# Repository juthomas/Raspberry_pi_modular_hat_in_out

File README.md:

# Raspberry Pi hat with inputs and outputs for modular synthesizer 

## Schematics

- [Link to pdf](https://github.com/juthomas/Raspberry_pi_modular_hat_in_out/blob/master/Schematics%20PDF/Modular_hat_in_out.pdf)

## Bill Of Materials

- [Link to IBOM](https://juthomas.github.io/Raspberry_pi_modular_hat_in_out/)

## Components

- [MCP3008](https://www.lcsc.com/product-detail/Analog-To-Digital-Converters-ADCs_Microchip-Tech-MCP3008-I-SL_C1520159.html) C1520159

- [LM324](https://www.lcsc.com/product-detail/Operational-Amplifier_STMicroelectronics-LM324DT_C71035.html) C71035

- [MCP4728](https://www.lcsc.com/product-detail/Digital-To-Analog-Converters-DACs_Microchip-Tech-MCP4728-E-UN_C108207.html) C108207

## C code examples (clean naming)

- Input reader: `C_code_example/inputs/src/input_reader.c`
  - binary name: `input_reader`
- Output generator: `C_code_example/outputs/src/output_generator.c`
  - binary name: `output_generator`
- Input/Output loopback tester: `C_code_example/input_outputs/src/input_output_tester.c`
  - binary name: `input_output_tester`

## Install dependencies and configure I2C (recommended)

Use the setup script:

`sudo ./scripts/install_rpi_dependencies.sh --baudrate 1000000`

What it does:

- installs apt dependencies (`build-essential`, `cmake`, `git`, `pkg-config`, `libgpiod-dev`, `i2c-tools`)
- installs [spidev-lib](https://github.com/juthomas/spidev-lib) in `/usr/local`
- sets `dtparam=i2c_arm=on,i2c_arm_baudrate=1000000`
- ensures `dtparam=spi=on`
- keeps a backup of `config.txt` before editing

Reboot is required after running the script.

### Manual install (if needed)

`sudo apt install build-essential cmake git pkg-config libgpiod-dev i2c-tools`

`git clone https://github.com/juthomas/spidev-lib.git`

`cd spidev-lib && mkdir -p build && cd build && cmake .. && make -j$(nproc) && sudo make install`

Do not forget to link with `-lspidev-lib` when compiling C code.

## Shell autocompletion for CLI options

The repository includes completion scripts for:

- `output_generator`
- `input_output_tester`
- `install_rpi_dependencies.sh`

Zsh (current session):

`source scripts/completions/rpi_hat_tools.zsh`

Zsh (persistent):

`echo 'source /absolute/path/to/Raspberry_pi_modular_hat_in_out/scripts/completions/rpi_hat_tools.zsh' >> ~/.zshrc`

Bash (current session):

`source scripts/completions/rpi_hat_tools.bash`

Bash (persistent):

`echo 'source /absolute/path/to/Raspberry_pi_modular_hat_in_out/scripts/completions/rpi_hat_tools.bash' >> ~/.bashrc`

## Build and run

Input side (ADC):

`cd C_code_example/inputs && make && ./input_reader`

With runtime options:

`cd C_code_example/inputs && make && ./input_reader --delay-us=100000`

Dashboard cadence is controlled in source with `EQUALIZER_EVERY` and `HISTORY_EVERY` in `C_code_example/inputs/src/input_reader.c`.

Output side (MCP4728):

`cd C_code_example/outputs && make && ./output_generator`

With runtime options:

`cd C_code_example/outputs && make && ./output_generator --resolution=1000 --delay-us=1`

Dashboard cadence is controlled in source with `EQUALIZER_EVERY` and `HISTORY_EVERY` in `C_code_example/outputs/src/output_generator.c`.

Input/Output combined test (MCP4728 sine with per-channel phase + ADS monitoring):

`cd C_code_example/input_outputs && make && ./input_output_tester --resolution=1000 --delay-us=1`

Dashboard cadence is controlled in source with `EQUALIZER_EVERY` and `HISTORY_EVERY` in `C_code_example/input_outputs/src/input_output_tester.c`.

## Electrical Voltage dividers & multiplier

### Divider
https://tinyurl.com/24boqd2k

### Multiplier
<!-- https://tinyurl.com/27d8ra9q -->
https://tinyurl.com/2aczbd22

https://github.com/WiringPi/WiringPi

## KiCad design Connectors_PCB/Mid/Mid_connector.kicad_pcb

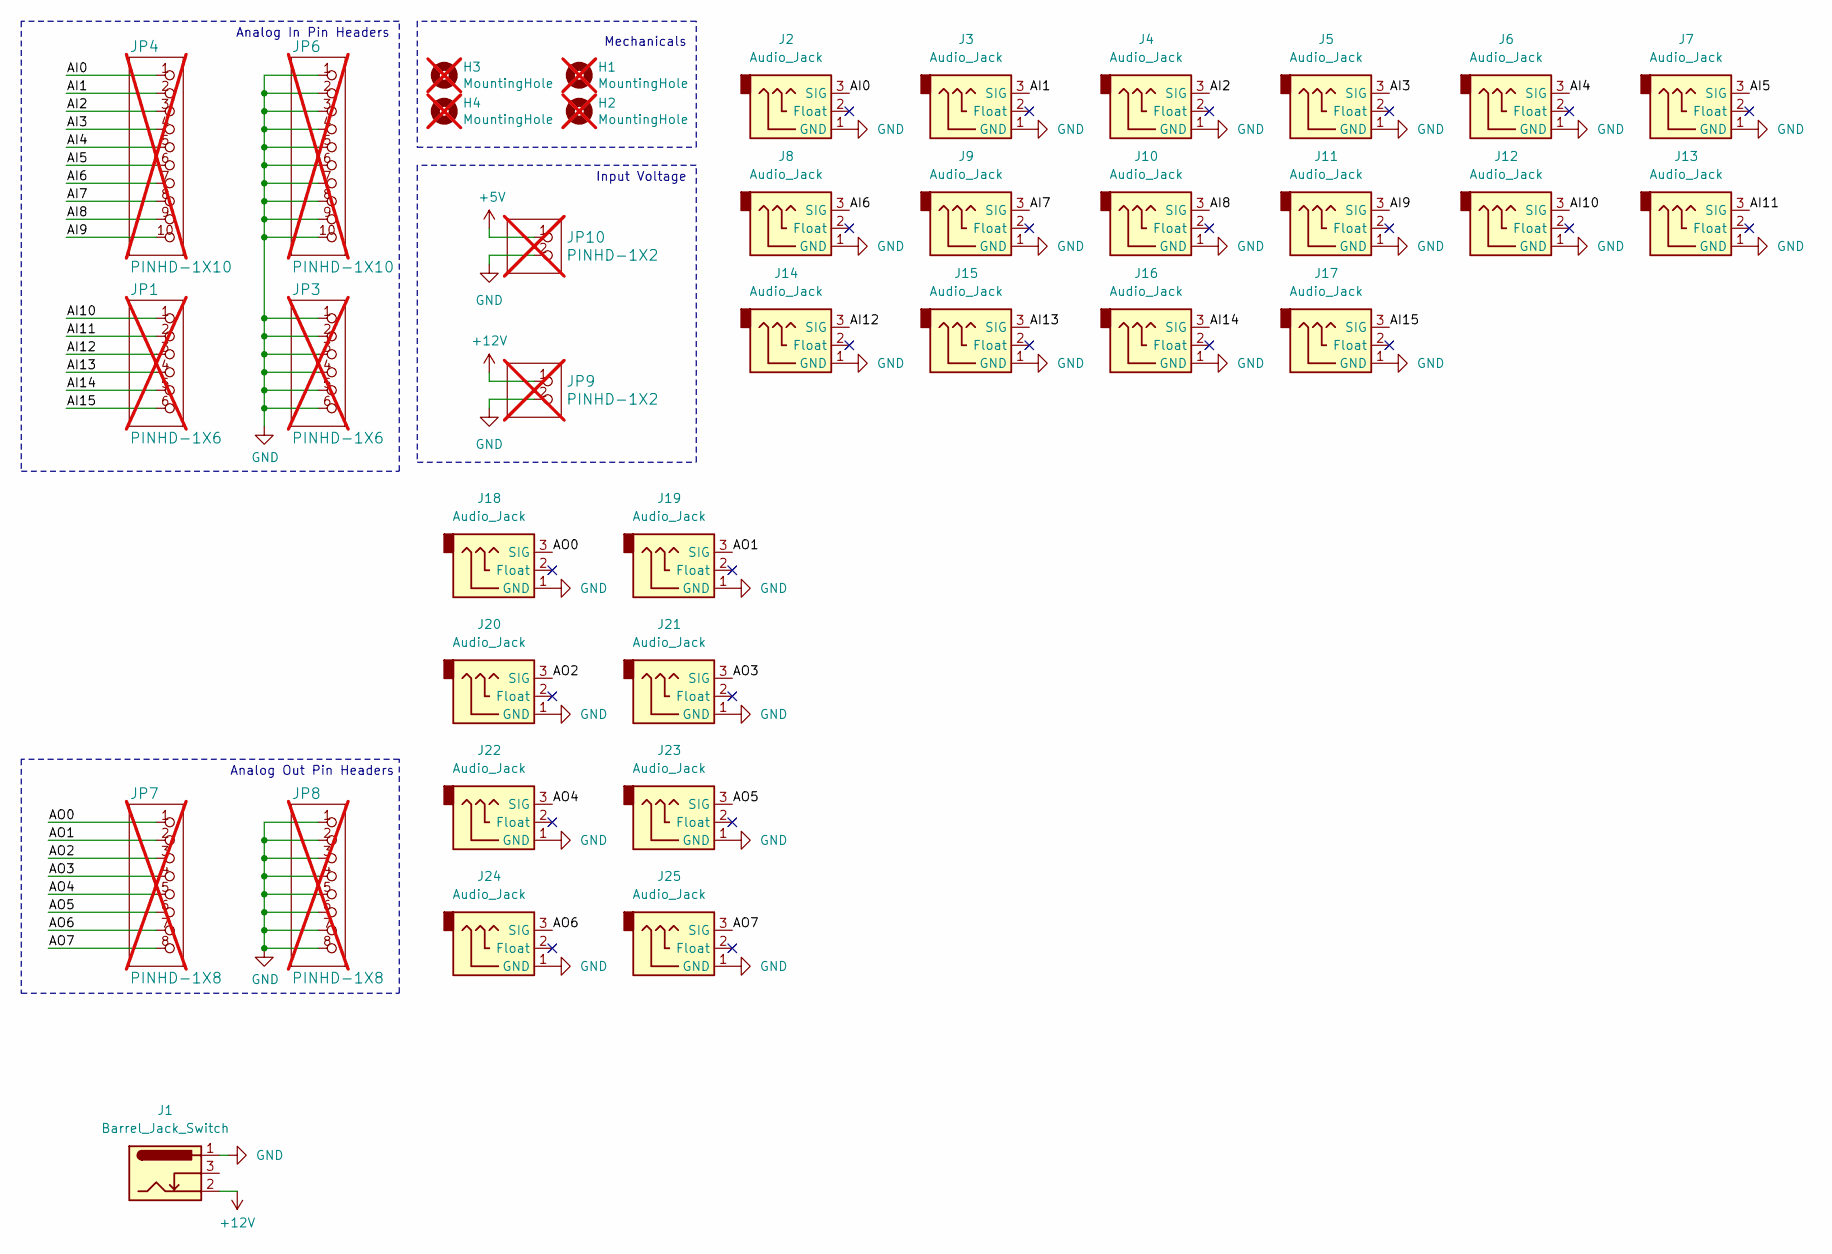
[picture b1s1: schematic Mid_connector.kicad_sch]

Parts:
H1, H2, H3, H4: MountingHole; MountingHole_2.7mm_M2.5; not fitted
J1: Barrel_Jack_Switch; DC_Jack_2.1
J2, J3, J4, J5, J6, J7, J8, J9, J10, J11, J12, J13, J14, J15, J16, J17, J18, J19, J20, J21, J22, J23, J24, J25: Audio_Jack; Mini_Jack
JP1, JP3: PINHD-1X6; 1X06-BIG; not fitted
JP4, JP6: PINHD-1X10; 1X10-BIG; not fitted
JP7, JP8: PINHD-1X8; 1X08-BIG; not fitted
JP9, JP10: PINHD-1X2; 1X02-BIG; not fitted

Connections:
+5V: JP10.1
+12V: J1.2, JP9.1
/AI0: J2.3 (SIG), JP4.1
/AI1: J3.3 (SIG), JP4.2
/AI2: J4.3 (SIG), JP4.3
/AI3: J5.3 (SIG), JP4.4
/AI4: J6.3 (SIG), JP4.5
/AI5: J7.3 (SIG), JP4.6
/AI6: J8.3 (SIG), JP4.7
/AI7: J9.3 (SIG), JP4.8
/AI8: J10.3 (SIG), JP4.9
/AI9: J11.3 (SIG), JP4.10
/AI10: J12.3 (SIG), JP1.1
/AI11: J13.3 (SIG), JP1.2
/AI12: J14.3 (SIG), JP1.3
/AI13: J15.3 (SIG), JP1.4
/AI14: J16.3 (SIG), JP1.5
/AI15: J17.3 (SIG), JP1.6
/AO0: J18.3 (SIG), JP7.1
/AO1: J19.3 (SIG), JP7.2
/AO2: J20.3 (SIG), JP7.3
/AO3: J21.3 (SIG), JP7.4
/AO4: J22.3 (SIG), JP7.5
/AO5: J23.3 (SIG), JP7.6
/AO6: J24.3 (SIG), JP7.7
/AO7: J25.3 (SIG), JP7.8
GND: J1.1, J2.1 (GND), J3.1 (GND), J4.1 (GND), J5.1 (GND), J6.1 (GND), J7.1 (GND), J8.1 (GND), J9.1 (GND), J10.1 (GND), J11.1 (GND), J12.1 (GND), J13.1 (GND), J14.1 (GND), J15.1 (GND), J16.1 (GND), J17.1 (GND), J18.1 (GND), J19.1 (GND), J20.1 (GND), J21.1 (GND), J22.1 (GND), J23.1 (GND), J24.1 (GND), J25.1 (GND), JP3.1, JP3.2, JP3.3, JP3.4, JP3.5, JP3.6, JP6.1, JP6.2, JP6.3, JP6.4, JP6.5, JP6.6, JP6.7, JP6.8, JP6.9, JP6.10, JP8.1, JP8.2, JP8.3, JP8.4, JP8.5, JP8.6, JP8.7, JP8.8, JP9.2, JP10.2

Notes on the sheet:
Analog Out Pin Headers
Mechanicals
Input Voltage
Analog In Pin Headers

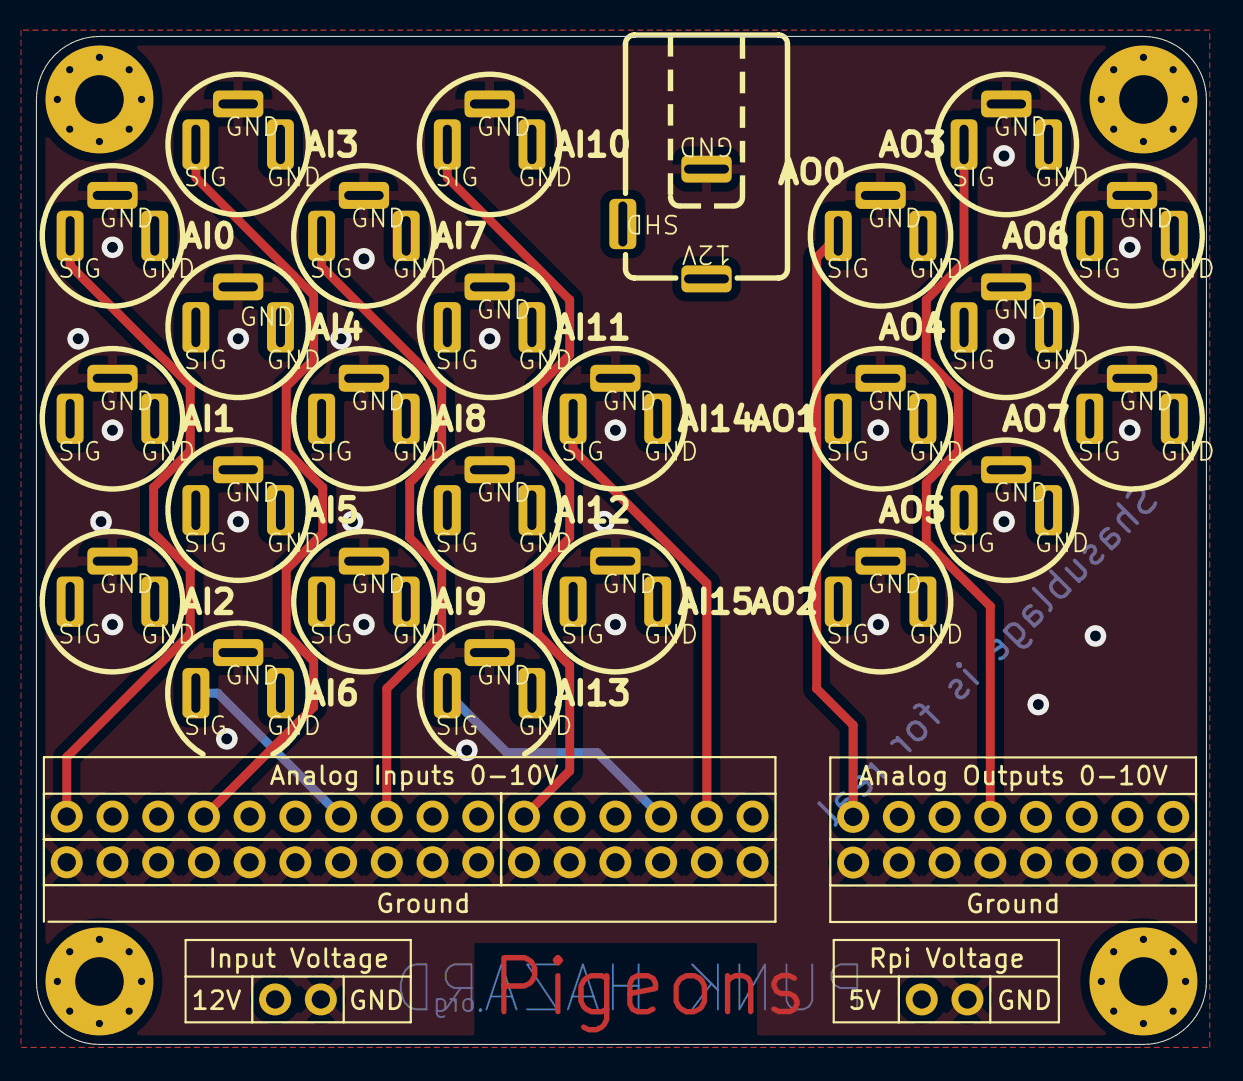
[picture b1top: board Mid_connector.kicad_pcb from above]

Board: 4 copper layers, 65.0 x 56.0 mm, 37 parts (0 on the bottom side), 26 nets.

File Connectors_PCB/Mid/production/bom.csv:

Designator,Footprint,Quantity,Value,LCSC Part #
J1,DC_Jack_2.1,1,Barrel_Jack_Switch,
"J10, J11, J12, J13, J14, J15, J16, J17, J18, J19, J2, J20, J21, J22, J23, J24, J25, J3, J4, J5, J6, J7, J8, J9",Mini_Jack,24,Audio_Jack,
"JP10, JP9",1X02-BIG,2,PINHD-1X2,

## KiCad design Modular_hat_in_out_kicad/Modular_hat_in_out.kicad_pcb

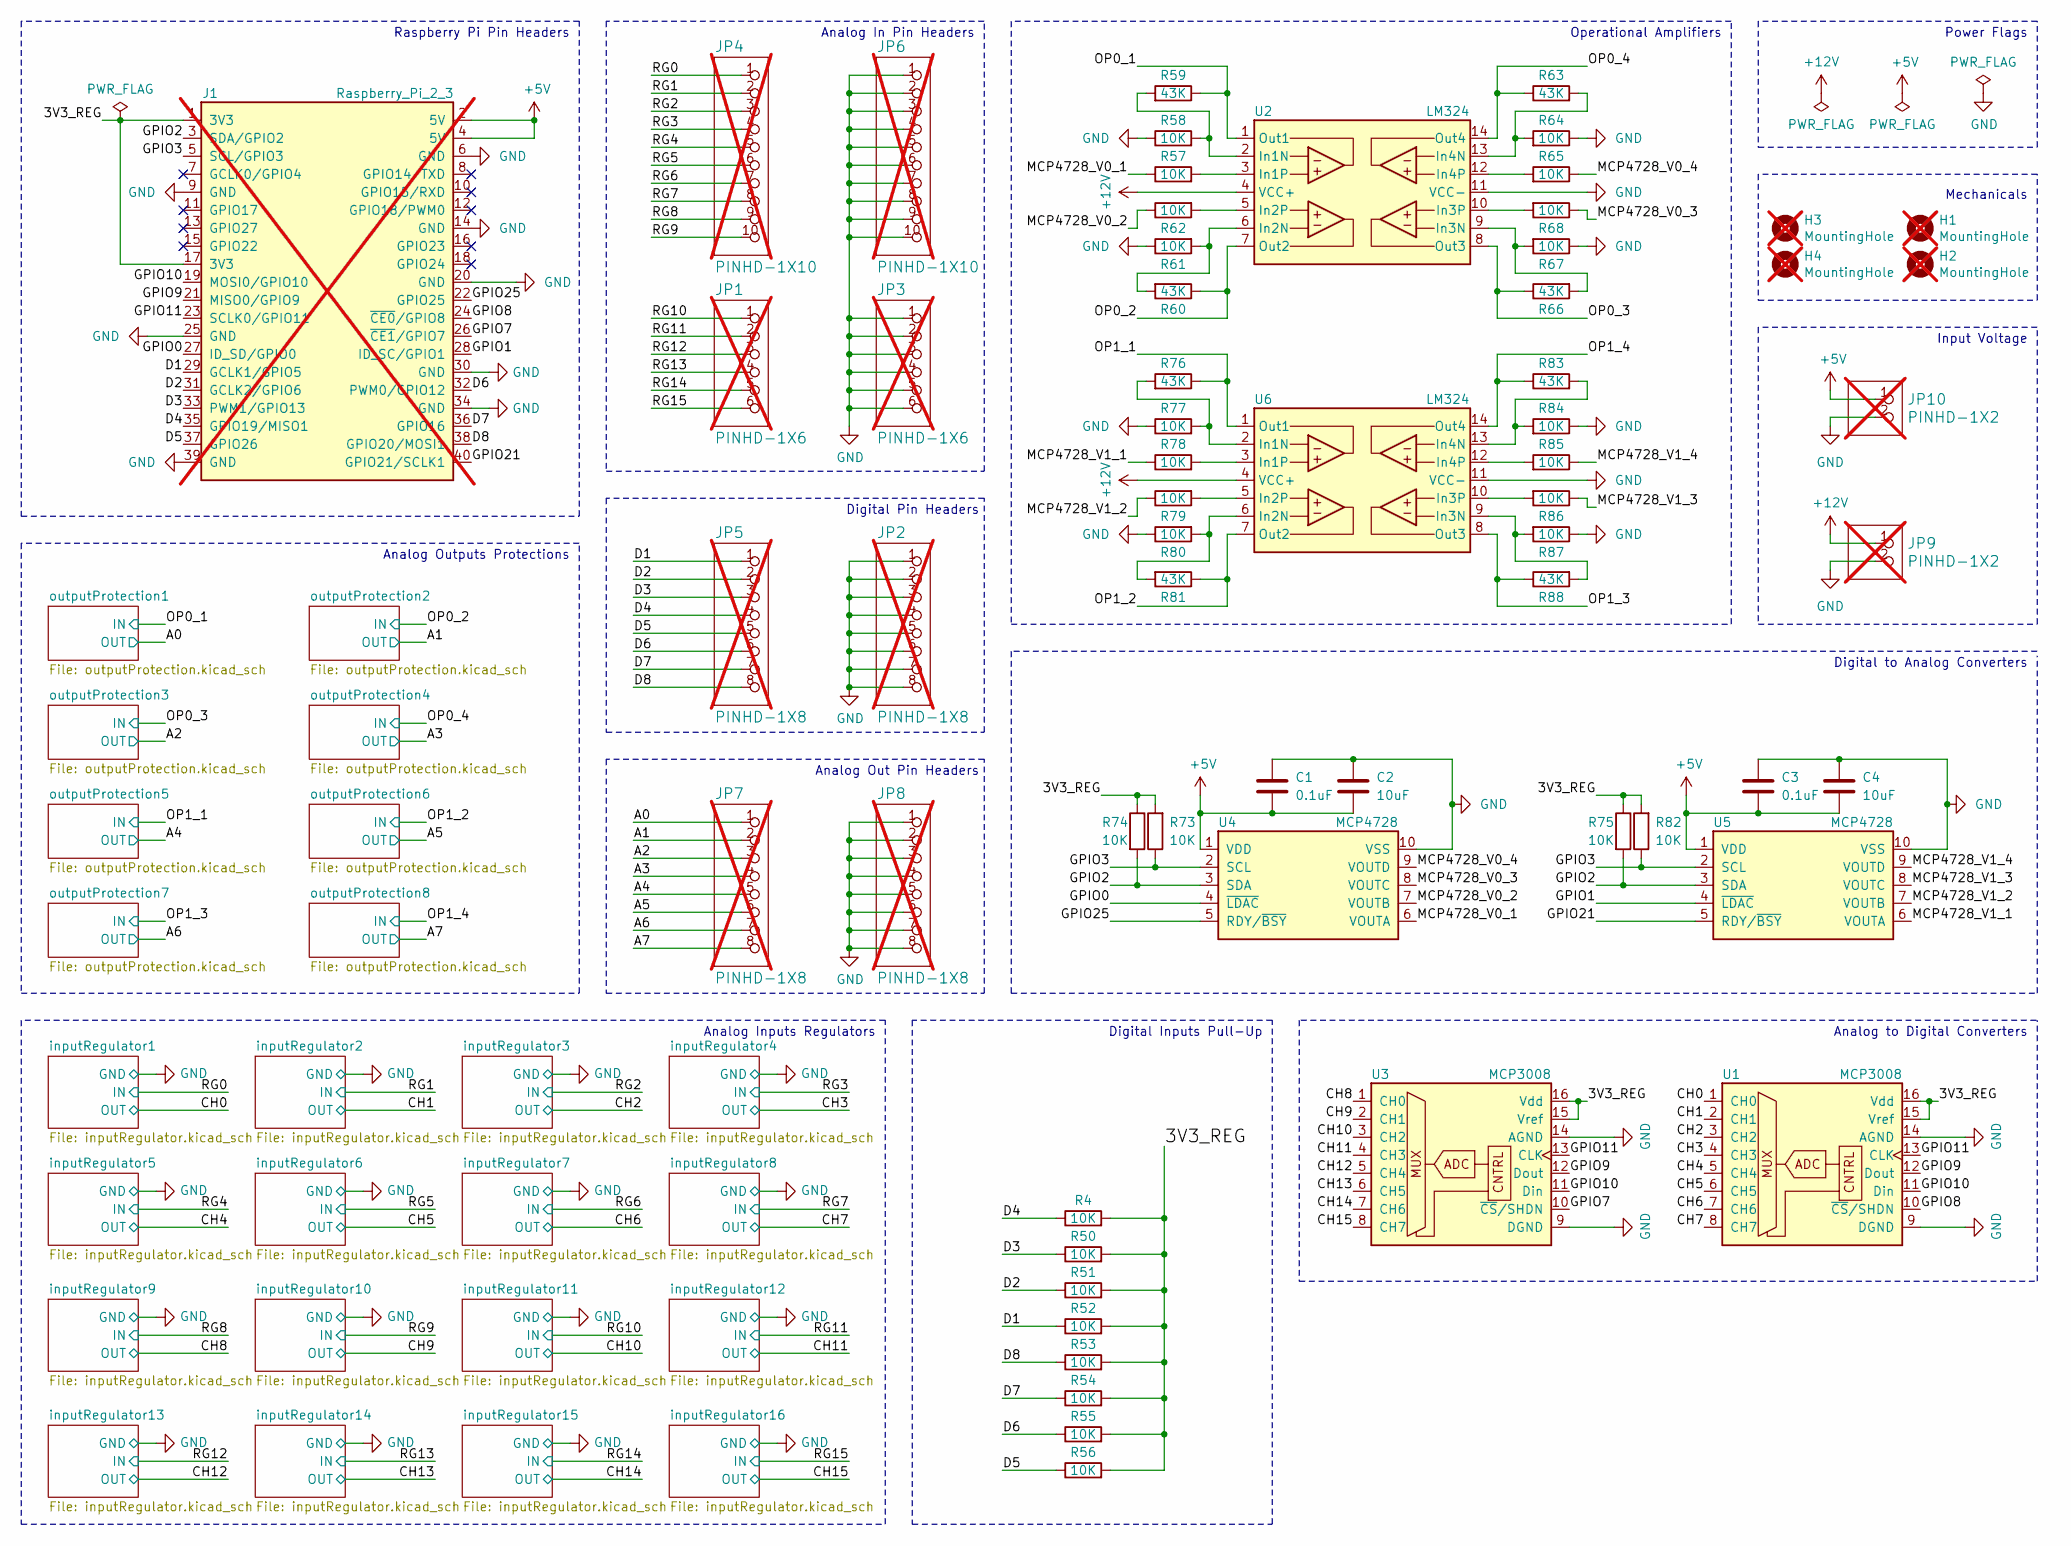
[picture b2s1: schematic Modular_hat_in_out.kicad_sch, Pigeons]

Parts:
C1, C3: 0.1uF; C_0603_1608Metric; LCSC C14663
C2, C4: 10uF; C_0603_1608Metric; LCSC C1691
H1, H2, H3, H4: MountingHole; MountingHole_2.7mm_M2.5; not fitted
J1: Raspberry_Pi_2_3; PIN_20X2; not fitted
JP1, JP3: PINHD-1X6; 1X06-BIG; not fitted
JP2, JP5, JP7, JP8: PINHD-1X8; 1X08-BIG; not fitted
JP4, JP6: PINHD-1X10; 1X10-BIG; not fitted
JP9, JP10: PINHD-1X2; 1X02-BIG; not fitted
R4, R50, R51, R52, R53, R54, R55, R56, R57, R58, R61, R62, R64, R65, R67, R68, R73, R74, R75, R77, R78, R79, R80, R82, R84, R85, R86, R87: 10K; R_0603_1608Metric; LCSC C25804
R59, R60, R63, R66, R76, R81, R83, R88: 43K; R_0603_1608Metric; LCSC C23172
U1, U3: MCP3008; MCP3008 SOIC16; LCSC C1520159
U2, U6: LM324; LM324 SOIC14; LCSC C71035
U4, U5: MCP4728; MCP4728 MSOP10; LCSC C108207

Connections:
+5V: C1.1, C2.1, C3.1, C4.1, J1.2 (5V), J1.4 (5V), JP10.1, U4.1 (VDD), U5.1 (VDD)
+12V: JP9.1, U2.4 (VCC+), U6.4 (VCC+)
/3V3_REG: J1.1 (3V3), J1.17 (3V3), R4.2, R50.2, R51.2, R52.2, R53.2, R54.2, R55.2, R56.2, R73.2, R74.1, R75.1, R82.2, U1.15 (Vref), U1.16 (Vdd), U3.15 (Vref), U3.16 (Vdd)
/A0: JP7.1; also elsewhere on the board
/A1: JP7.2; also elsewhere on the board
/A2: JP7.3; also elsewhere on the board
/A3: JP7.4; also elsewhere on the board
/A4: JP7.5; also elsewhere on the board
/A5: JP7.6; also elsewhere on the board
/A6: JP7.7; also elsewhere on the board
/A7: JP7.8; also elsewhere on the board
/CH0: U1.1 (CH0); also elsewhere on the board
/CH1: U1.2 (CH1); also elsewhere on the board
/CH2: U1.3 (CH2); also elsewhere on the board
/CH3: U1.4 (CH3); also elsewhere on the board
/CH4: U1.5 (CH4); also elsewhere on the board
/CH5: U1.6 (CH5); also elsewhere on the board
/CH6: U1.7 (CH6); also elsewhere on the board
/CH7: U1.8 (CH7); also elsewhere on the board
/CH8: U3.1 (CH0); also elsewhere on the board
/CH9: U3.2 (CH1); also elsewhere on the board
/CH10: U3.3 (CH2); also elsewhere on the board
/CH11: U3.4 (CH3); also elsewhere on the board
/CH12: U3.5 (CH4); also elsewhere on the board
/CH13: U3.6 (CH5); also elsewhere on the board
/CH14: U3.7 (CH6); also elsewhere on the board
/CH15: U3.8 (CH7); also elsewhere on the board
/D1: J1.29 (GCLK1/GPIO5), JP5.1, R52.1
/D2: J1.31 (GCLK2/GPIO6), JP5.2, R51.1
/D3: J1.33 (PWM1/GPIO13), JP5.3, R50.1
/D4: J1.35 (GPIO19/MISO1), JP5.4, R4.1
/D5: J1.37 (GPIO26), JP5.5, R56.1
/D6: J1.32 (PWM0/GPIO12), JP5.6, R55.1
/D7: J1.36 (GPIO16), JP5.7, R54.1
/D8: J1.38 (GPIO20/MOSI1), JP5.8, R53.1
/GPIO0: J1.27 (ID_SD/GPIO0), U4.4 (~LDAC)
/GPIO1: J1.28 (ID_SC/GPIO1), U5.4 (~LDAC)
/GPIO2: J1.3 (SDA/GPIO2), R74.2, R75.2, U4.3 (SDA), U5.3 (SDA)
/GPIO3: J1.5 (SCL/GPIO3), R73.1, R82.1, U4.2 (SCL), U5.2 (SCL)
/GPIO7: J1.26 (~CE1/GPIO7), U3.10 (~CS/SHDN)
/GPIO8: J1.24 (~CE0/GPIO8), U1.10 (~CS/SHDN)
/GPIO9: J1.21 (MISO0/GPIO9), U1.12 (Dout), U3.12 (Dout)
/GPIO10: J1.19 (MOSI0/GPIO10), U1.11 (Din), U3.11 (Din)
/GPIO11: J1.23 (SCLK0/GPIO11), U1.13 (CLK), U3.13 (CLK)
/GPIO21: J1.40 (GPIO21/SCLK1), U5.5 (RDY/~BSY)
/GPIO25: J1.22 (GPIO25), U4.5 (RDY/~BSY)
/MCP4728_V0_1: R57.1, U4.6 (VOUTA)
/MCP4728_V0_2: R62.1, U4.7 (VOUTB)
/MCP4728_V0_3: R68.1, U4.8 (VOUTC)
/MCP4728_V0_4: R65.1, U4.9 (VOUTD)
/MCP4728_V1_1: R78.1, U5.6 (VOUTA)
/MCP4728_V1_2: R79.1, U5.7 (VOUTB)
/MCP4728_V1_3: R86.1, U5.8 (VOUTC)
/MCP4728_V1_4: R85.1, U5.9 (VOUTD)
/OP0_1: R59.2, U2.1 (Out1); also elsewhere on the board
/OP0_2: R60.2, U2.7 (Out2); also elsewhere on the board
/OP0_3: R66.2, U2.8 (Out3); also elsewhere on the board
/OP0_4: R63.2, U2.14 (Out4); also elsewhere on the board
/OP1_1: R76.2, U6.1 (Out1); also elsewhere on the board
/OP1_2: R81.2, U6.7 (Out2); also elsewhere on the board
/OP1_3: R88.2, U6.8 (Out3); also elsewhere on the board
/OP1_4: R83.2, U6.14 (Out4); also elsewhere on the board
/RG0: JP4.1; also elsewhere on the board
/RG1: JP4.2; also elsewhere on the board
/RG2: JP4.3; also elsewhere on the board
/RG3: JP4.4; also elsewhere on the board
/RG4: JP4.5; also elsewhere on the board
/RG5: JP4.6; also elsewhere on the board
/RG6: JP4.7; also elsewhere on the board
/RG7: JP4.8; also elsewhere on the board
/RG8: JP4.9; also elsewhere on the board
/RG9: JP4.10; also elsewhere on the board
/RG10: JP1.1; also elsewhere on the board
/RG11: JP1.2; also elsewhere on the board
/RG12: JP1.3; also elsewhere on the board
/RG13: JP1.4; also elsewhere on the board
/RG14: JP1.5; also elsewhere on the board
/RG15: JP1.6; also elsewhere on the board
GND: C1.2, C2.2, C3.2, C4.2, J1.6 (GND), J1.9 (GND), J1.14 (GND), J1.20 (GND), J1.25 (GND), J1.30 (GND), J1.34 (GND), J1.39 (GND), JP2.1, JP2.2, JP2.3, JP2.4, JP2.5, JP2.6, JP2.7, JP2.8, JP3.1, JP3.2, JP3.3, JP3.4, JP3.5, JP3.6, JP6.1, JP6.2, JP6.3, JP6.4, JP6.5, JP6.6, JP6.7, JP6.8, JP6.9, JP6.10, JP8.1, JP8.2, JP8.3, JP8.4, JP8.5, JP8.6, JP8.7, JP8.8, JP9.2, JP10.2, R58.1, R61.1, R64.1, R67.1, R77.1, R80.1, R84.1, R87.1, U1.9 (DGND), U1.14 (AGND), U2.11 (VCC-), U3.9 (DGND), U3.14 (AGND), U4.10 (VSS), U5.10 (VSS), U6.11 (VCC-); also elsewhere on the board
unnamed: R58.2, R59.1, U2.2 (In1N)
unnamed: R57.2, U2.3 (In1P)
unnamed: R60.1, R61.2, U2.6 (In2N)
unnamed: R62.2, U2.5 (In2P)
unnamed: R66.1, R67.2, U2.9 (In3N)
unnamed: R68.2, U2.10 (In3P)
unnamed: R63.1, R64.2, U2.13 (In4N)
unnamed: R65.2, U2.12 (In4P)
unnamed: R76.1, R77.2, U6.2 (In1N)
unnamed: R78.2, U6.3 (In1P)
unnamed: R80.2, R81.1, U6.6 (In2N)
unnamed: R79.2, U6.5 (In2P)
unnamed: R87.2, R88.1, U6.9 (In3N)
unnamed: R86.2, U6.10 (In3P)
unnamed: R83.1, R84.2, U6.13 (In4N)
unnamed: R85.2, U6.12 (In4P)

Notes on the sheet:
Analog Outputs Protections
Digital Inputs Pull-Up
Analog Out Pin Headers
Raspberry Pi Pin Headers
Operational Amplifiers
Input Voltage
Mechanicals
Analog Inputs Regulators
Digital Pin Headers
Digital to Analog Converters
Analog In Pin Headers
Analog to Digital Converters
Power Flags

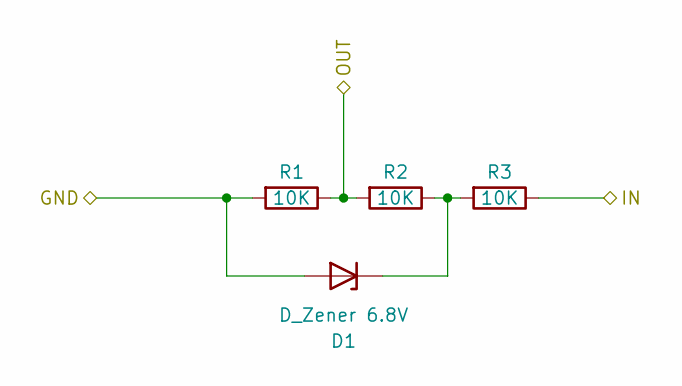
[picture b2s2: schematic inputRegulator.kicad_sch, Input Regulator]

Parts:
D1: D_Zener 6.8V; D_Z_0603_1608Metric; LCSC C2832575
R1, R2, R3: 10K; R_0603_1608Metric; LCSC C25804

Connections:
/CH0: R1.1, R2.2; also elsewhere on the board
/RG0: R3.1; also elsewhere on the board
GND: D1.2 (A), R1.2; also elsewhere on the board
unnamed: D1.1 (K), R2.1, R3.2

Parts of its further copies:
D2, D3, D4, D5, D6, D7, D8, D9, D10, D11, D12, D13, D14, D15, D16: D_Zener 6.8V; D_Z_0603_1608Metric; LCSC C2832575
R5, R6, R7, R8, R9, R10, R11, R12, R13, R14, R15, R16, R17, R18, R19, R20, R21, R22, R23, R24, R25, R26, R27, R28, R29, R30, R31, R32, R33, R34, R35, R36, R37, R38, R39, R40, R41, R42, R43, R44, R45, R46, R47, R48, R49: 10K; R_0603_1608Metric; LCSC C25804

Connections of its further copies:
/CH1: R5.1, R6.2; also elsewhere on the board
/CH2: R8.1, R9.2; also elsewhere on the board
/CH3: R11.1, R12.2; also elsewhere on the board
/CH4: R14.1, R15.2; also elsewhere on the board
/CH5: R17.1, R18.2; also elsewhere on the board
/CH6: R20.1, R21.2; also elsewhere on the board
/CH7: R23.1, R24.2; also elsewhere on the board
/CH8: R26.1, R27.2; also elsewhere on the board
/CH9: R29.1, R30.2; also elsewhere on the board
/CH10: R32.1, R33.2; also elsewhere on the board
/CH11: R35.1, R36.2; also elsewhere on the board
/CH12: R38.1, R39.2; also elsewhere on the board
/CH13: R41.1, R42.2; also elsewhere on the board
/CH14: R44.1, R45.2; also elsewhere on the board
/CH15: R47.1, R48.2; also elsewhere on the board
/RG1: R7.1; also elsewhere on the board
/RG2: R10.1; also elsewhere on the board
/RG3: R13.1; also elsewhere on the board
/RG4: R16.1; also elsewhere on the board
/RG5: R19.1; also elsewhere on the board
/RG6: R22.1; also elsewhere on the board
/RG7: R25.1; also elsewhere on the board
/RG8: R28.1; also elsewhere on the board
/RG9: R31.1; also elsewhere on the board
/RG10: R34.1; also elsewhere on the board
/RG11: R37.1; also elsewhere on the board
/RG12: R40.1; also elsewhere on the board
/RG13: R43.1; also elsewhere on the board
/RG14: R46.1; also elsewhere on the board
/RG15: R49.1; also elsewhere on the board
GND: D2.2 (A), D3.2 (A), D4.2 (A), D5.2 (A), D6.2 (A), D7.2 (A), D8.2 (A), D9.2 (A), D10.2 (A), D11.2 (A), D12.2 (A), D13.2 (A), D14.2 (A), D15.2 (A), D16.2 (A), R5.2, R8.2, R11.2, R14.2, R17.2, R20.2, R23.2, R26.2, R29.2, R32.2, R35.2, R38.2, R41.2, R44.2, R47.2; also elsewhere on the board
unnamed: D2.1 (K), R6.1, R7.2
unnamed: D3.1 (K), R9.1, R10.2
unnamed: D4.1 (K), R12.1, R13.2
unnamed: D5.1 (K), R15.1, R16.2
unnamed: D6.1 (K), R18.1, R19.2
unnamed: D7.1 (K), R21.1, R22.2
unnamed: D8.1 (K), R24.1, R25.2
unnamed: D9.1 (K), R27.1, R28.2
unnamed: D10.1 (K), R30.1, R31.2
unnamed: D11.1 (K), R33.1, R34.2
unnamed: D12.1 (K), R36.1, R37.2
unnamed: D13.1 (K), R39.1, R40.2
unnamed: D14.1 (K), R42.1, R43.2
unnamed: D15.1 (K), R45.1, R46.2
unnamed: D16.1 (K), R48.1, R49.2

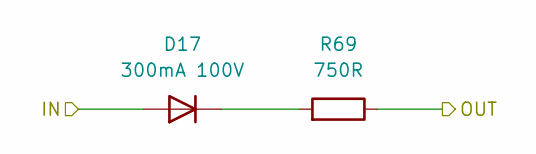
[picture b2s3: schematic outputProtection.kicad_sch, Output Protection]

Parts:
D17: 300mA 100V; D_0603_1608Metric; LCSC C727112
R69: 750R; R_0603_1608Metric; LCSC C23241

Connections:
/A0: R69.2; also elsewhere on the board
/OP0_1: D17.2 (A); also elsewhere on the board
unnamed: D17.1 (K), R69.1

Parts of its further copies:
D18, D19, D20, D21, D22, D23, D24: 300mA 100V; D_0603_1608Metric; LCSC C727112
R70, R71, R72, R89, R90, R91, R92: 750R; R_0603_1608Metric; LCSC C23241

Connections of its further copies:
/A1: R70.2; also elsewhere on the board
/A2: R71.2; also elsewhere on the board
/A3: R72.2; also elsewhere on the board
/A4: R89.2; also elsewhere on the board
/A5: R90.2; also elsewhere on the board
/A6: R91.2; also elsewhere on the board
/A7: R92.2; also elsewhere on the board
/OP0_2: D18.2 (A); also elsewhere on the board
/OP0_3: D19.2 (A); also elsewhere on the board
/OP0_4: D20.2 (A); also elsewhere on the board
/OP1_1: D21.2 (A); also elsewhere on the board
/OP1_2: D22.2 (A); also elsewhere on the board
/OP1_3: D23.2 (A); also elsewhere on the board
/OP1_4: D24.2 (A); also elsewhere on the board
unnamed: D18.1 (K), R70.1
unnamed: D19.1 (K), R71.1
unnamed: D20.1 (K), R72.1
unnamed: D21.1 (K), R89.1
unnamed: D22.1 (K), R90.1
unnamed: D23.1 (K), R91.1
unnamed: D24.1 (K), R92.1

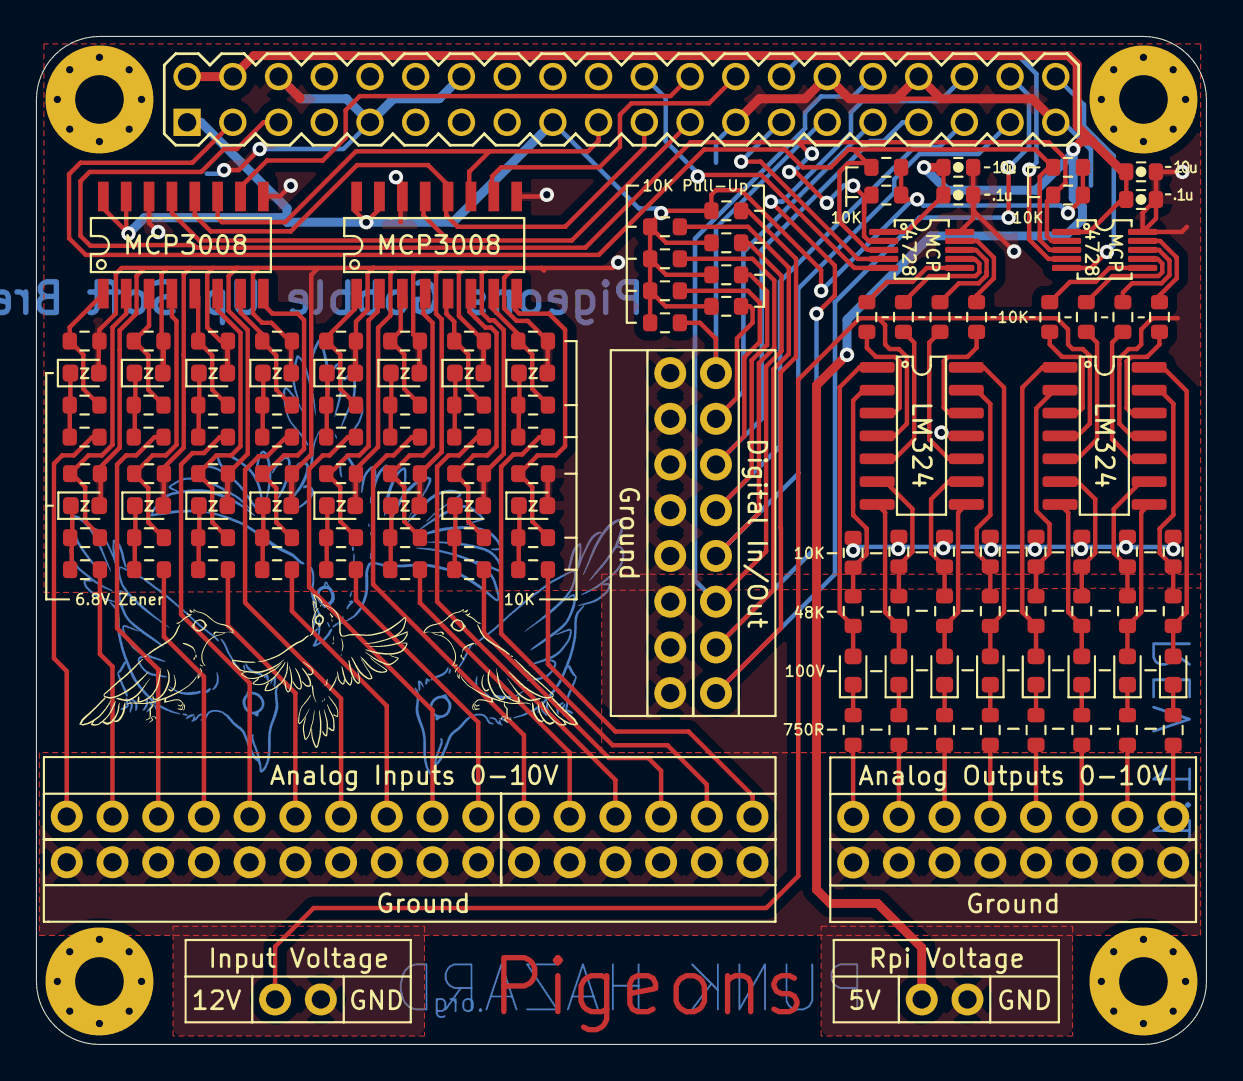
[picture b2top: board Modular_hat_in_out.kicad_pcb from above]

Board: 2 copper layers, 65.0 x 56.0 mm, 141 parts (0 on the bottom side), 119 nets.

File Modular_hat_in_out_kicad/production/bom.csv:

Designator,Footprint,Quantity,Value,LCSC Part #
"C1, C3",0603,2,0.1uF,C14663
"C2, C4",0603,2,10uF,C1691
"D1, D10, D11, D12, D13, D14, D15, D16, D2, D3, D4, D5, D6, D7, D8, D9",0603,16,D_Zener 6.8V,C2832575
"D17, D18, D19, D20, D21, D22, D23, D24",0603,8,300mA 100V,C727112
"R1, R10, R11, R12, R13, R14, R15, R16, R17, R18, R19, R2, R20, R21, R22, R23, R24, R25, R26, R27, R28, R29, R3, R30, R31, R32, R33, R34, R35, R36, R37, R38, R39, R4, R40, R41, R42, R43, R44, R45, R46, R47, R48, R49, R5, R50, R51, R52, R53, R54, R55, R56, R57, R58, R6, R61, R62, R64, R65, R67, R68, R7, R73, R74, R75, R77, R78, R79, R8, R80, R82, R84, R85, R86, R87, R9",0603,76,10K,C25804
"R59, R60, R63, R66, R76, R81, R83, R88",0603,8,43K,C23172
"R69, R70, R71, R72, R89, R90, R91, R92",0603,8,750R,C23241
"U1, U3",MCP3008 SOIC16,2,MCP3008,C1520159
"U2, U6",LM324 SOIC14,2,LM324,C71035
"U4, U5",MCP4728 MSOP10,2,MCP4728,C108207

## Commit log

2023-11-15 [UDPT] Project name
2023-11-15 [ADD] LM324 & MCP4728 Shematics
2023-11-15 [UDPT] MCP3008 & LM324 & MCP4728
2023-11-15 [UDPT] MCP3008 in schematics
2023-11-15 [ADD] Connections and update configuration resistors
2023-11-15 [ADD] Update design and Schematics for 4 channels DAC seems OK
2023-11-27 [UDPT] Mounting Holes Upgraded
2023-12-13 [ADD] Schematics in progress
2023-12-14 [ERC] Major problems fixed
2023-12-15 [UDPT] Electrical design
2024-07-27 [ADD] Update to last kicad version
2024-07-27 [ADD] MCP4728 footprint
2024-07-27 [ADD] Footprints
2024-07-27 [ADD] LCSC Capacitor parts
2024-07-27 [ADD] ML324 footprint
2024-07-27 [CLEAN] PCB Editor
2024-07-27 [ADD] MCP3008 preplacement
2024-07-27 [ADD] LM324 preplacement
2024-07-27 [ADD] Tests for LM324 rooting
2024-07-28 [ADD] Routing LM324
2024-07-28 [ADD] Routing MCP4728
2024-07-28 [ADD] Some placements
2024-07-28 [ADD] Pre routing MCP3008
2024-07-28 [ADD] Digital routing
2024-07-28 [ADD] Routing digital
2024-07-29 [ADD] 12V input in shematics
2024-07-29 [ADD] All components routed
2024-07-29 [ADD] Some routing
2024-07-29 [ADD] Some GND routing
2024-07-29 [ADD] ERC & DRC OK
2024-07-29 [ADD] Some Silkcreen
2024-07-29 [ADD] Some pigeons
2024-07-29 [ADD] Somes pigeons
2024-07-29 [ADD] 2 Metalic pigeons
2024-07-29 [ADD] One more metalic pigeon
2024-07-29 [ADD] Pigeon citation
2024-07-30 [ADD] Some plants
2024-08-06 [ADD] Some drawings
2024-08-07 [UDPT] Mac se logo
2024-08-21 [ADD] Build for production
2024-08-21 [ADD] IBOM
2024-08-21 [ADD] Schematics PDF
2024-08-21 [ADD] Readme images
2024-08-21 [UDPT] Readme images
2024-08-21 [ADD] Revision number (1.0)
2024-08-21 [UDPT] 3D view with rev number
2024-08-21 [CLEAN] Build
2024-08-22 [UPDT] Silkscreen on some footprints
2024-08-22 [FIX] Update from schematics warning
2024-09-23 [ADD] last commit before bitbanging test
2025-01-27 [ADD] less buggy code
2025-01-27 [ADD] See p42 datasheet
2025-02-05 [ADD] Some infos on DAC
2025-10-27 [ADD] Test analog output
2025-10-27 [ADD] basic code working but overvoltage before ampli-op
2025-10-27 [ADD] All inputs individually tested
2025-10-28 [ADD] 5V Input voltage in schematics + clean
2025-10-28 [ADD] New Revision 1.1
2025-10-28 [UPDT] Html ibom
2025-11-27 [ADD] New Files
2025-12-04 [ADD] Mid PCB V1.0
2025-12-04 [ADD] First version of top pcb connectors
2026-02-18 [FIX] Analog outputs code
2026-02-18 [ADD] Parametrable resolution & delay
2026-02-18 [ADD] Equalizers & inputs_ouput test program
